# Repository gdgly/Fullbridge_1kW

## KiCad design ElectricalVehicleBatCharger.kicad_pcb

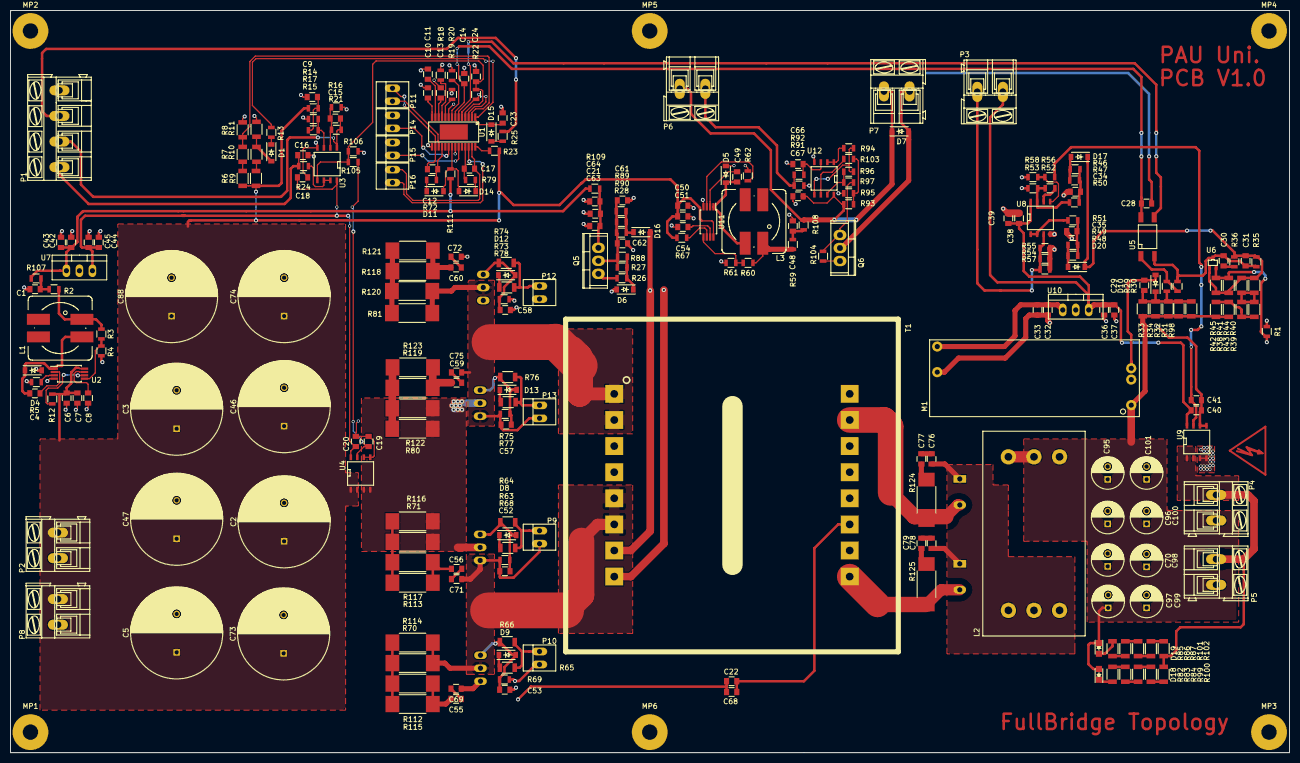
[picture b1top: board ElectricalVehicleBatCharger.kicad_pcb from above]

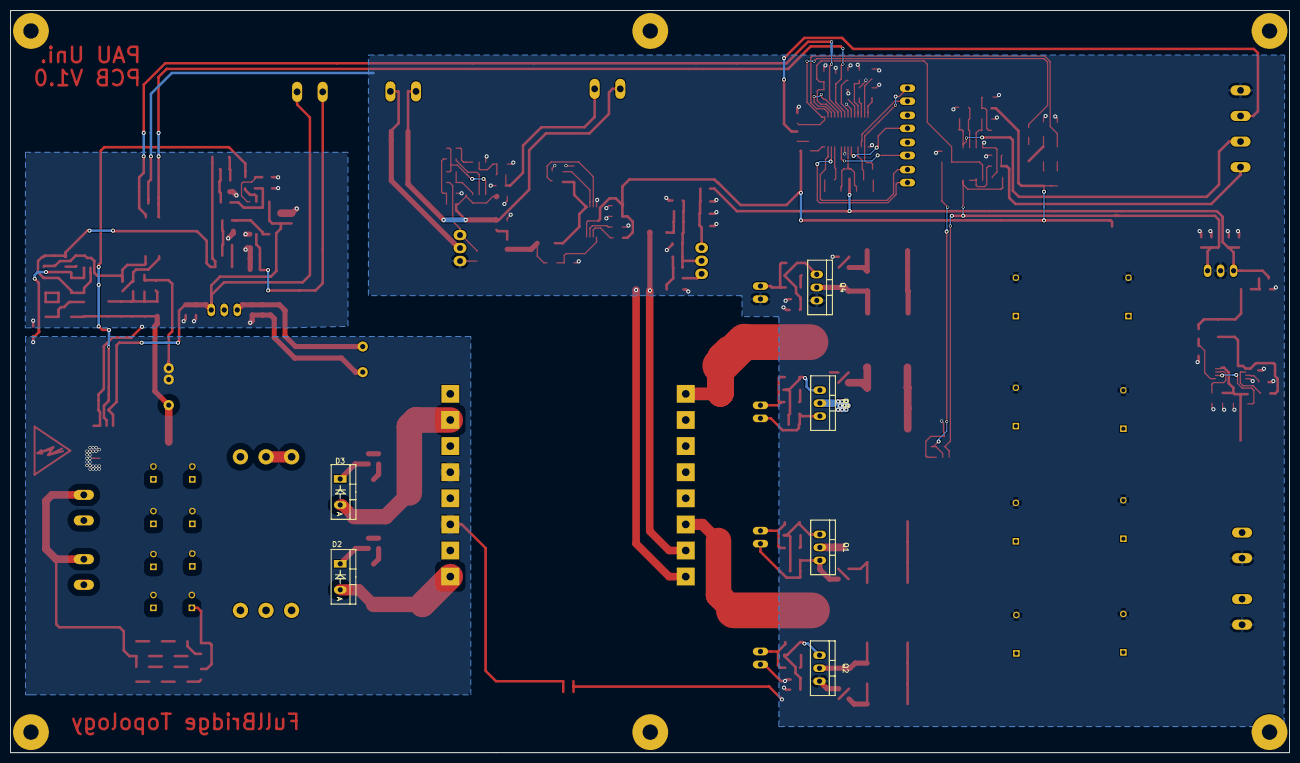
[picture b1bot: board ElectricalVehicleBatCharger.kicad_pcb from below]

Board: 2 copper layers, 249.9 x 145.0 mm, 271 parts (6 on the bottom side), 140 nets.

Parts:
C1, C4, C12, C17, C21, C48, C49, C62, C63, C64: CP1; C_0805
C2, C3, C5, C46, C47, C73, C74, C88: CP1; C_Radial_D18_L36_P7.5
C6, C7, C8, C9, C10, C11, C13, C14, C15, C23, C24, C28, C29, C30, C31, C32, C33, C34, C35, C36, C37, C38, C39, C42, C43, C44, C45, C50, C51, C52, C53, C54, C55, C56, C57, C58, C59, C60, C61, C66, C67, C69, C71, C72, C75, C76, C77, C78, C79: C; C_0805
C16, C18, C19: 1u; C_0805
C20, C22, C40, C41, C68: 100n; C_0805
C70, C95, C96, C97, C98, C99, C100, C101: CP1; C_Radial_D6.3_L11.2_P2.5
D1, D4, D5, D7, D8, D9, D11, D12, D13, D14, D15, D16, D17, D20: Diode; SOD-123
D2, D3: D_Schottky; Diode_TO-220_Vertical
D6, D10: ZENERsmall; SOD-123
D18: LED_Green; LED_0805
D19: LED_Red; LED_0805
L1, L3: INDUCTOR; Inductor_Double_SMD_12.5-Lx12.5-Wx6.2-H
L2: INDUCTOR_3; L_3
M1: Flyback; Flyback_Module_200mW
MP1, MP2, MP3, MP4, MP5, MP6: SCREW; SCREW_3mm
P1: CONN_01X04; AK300-4
P2, P3, P4, P5, P6, P7, P8: CONN_01X02; AK300-2
P9, P10, P11, P12, P13, P14, P15, P16: CONN_01X02; PINHEAD1-2
Q1, Q2, Q3, Q4: FDP083N15A; TO-220_Neutral123_Vertical
Q5: BD909; TO-220
Q6: IRF540N; TO-220
R1, R2, R3, R4, R5, R12, R13, R14, R15, R16, R17, R18, R19, R20, R21, R22, R23, R24, R25, R26, R27, R28, R29, R30, R35, R36, R46, R47, R48, R49, R50, R51, R52, R53, R54, R55, R56, R57, R58, R59, R60, R61, R62, R67, R68, R69, R72, R77, R78, R79, R88, R89, R90, R91, R92, R93, R94, R95, R96, R97, R104, R105, R106: R; R_0805
R6, R7, R8, R9, R10, R11, R31, R32, R33, R34, R38, R39, R40, R41, R42, R43, R44, R45, R63, R64, R65, R66, R73, R74, R75, R76, R98: R; R_1206
R70, R71, R80, R81, R112, R113, R114, R115, R116, R117, R118, R119, R120, R121, R122, R123, R124, R125: R; R_2512_HandSoldering
R82, R83, R84, R85, R86, R87, R99, R100, R101, R102: 22k; R_1206
R103: 10k; R_0805
R107, R108, R109: 0; R_0805
R111: NC; R_0805
T1: Transf_Type1; E65_Former
U1: LM5045; HTSSOP_9.70mmX4.40mm
U2, U11: LM5008; TSSOP-8_4.4x3mm_Pitch0.65mm
U3, U8, U12: LM358N; SOIC-8-N
U4, U9: ACS723; SOIC-8-N
U5: FOD817; Optocoupler_SMD_HandSoldering_KPC357_LTV35x_PC357_SingleCha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
U6: TL431; SOT-323
U7, U10: 7805; TO-220_Neutral123_Vertical

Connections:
+5V: C18.2, C20.2, C44.2, C45.2, U3.8, U4.8, U7.3
+5VD: C36.2, C37.2, C38.1, C39.2, C40.1, P3.1, U8.8, U9.8, U10.3
+12P: C32.2, C33.2, M1.5, U10.1
+12V: C67.1, D7.1, P6.2, P7.1, R93.1, R108.1, U12.8
+15V: C42.2, C43.2, R107.1, R109.2, R111.2, U7.1
/COMP: U1.6, U5.3
/Fan-: D7.2, P7.2, Q6.2
/HO1: P16.1, U1.26
/HO2: P11.1, U1.17
/Ip: C24.2, R22.1, R105.2, R106.1, U1.4, U3.5
/IpFiltered: C16.2, P1.1, R24.2
/LO1: P15.1, U1.23
/LO2: P14.1, U1.20
/Lo_Line: C76.2, C78.2, D2.1, D3.1, L2.1, L2.2, L2.3
/OVP: R7.2, R8.1, U1.2
/OnOff: P1.3, R25.1
/OutputPowerLine: C70.1, C95.1, C96.1, C97.1, C98.1, C99.1, C100.1, C101.1, D18.2, D19.1, L2.4, L2.5, L2.6, M1.1, P4.2, P5.2, R31.1, R32.1, R33.1, R34.1, R38.1, R42.1, R98.1
/OutputPowerLine_Return: P4.1, P5.1, R100.2, R102.2, U9.1, U9.2
/Q1_G: P9.2, R63.2, R64.2
/Q1_S: C52.1, C71.1, P9.1, Q1.3, Q2.2, R68.2, R70.1, R114.1, T1.5, T1.6
/Q2_G: P10.2, R65.2, R66.2
/Q3_G: P13.2, R75.2, R76.2
/Q3_S: C57.1, C75.2, P13.1, Q3.3, Q4.2, R77.2, R81.1, R120.1, T1.1, T1.2
/Q4_G: P12.2, R73.2, R74.2
/REF: C14.2, C28.1, U1.7, U5.4
/SHUTDOWN: R12.1, U2.6
/SHUTDOWN_FAN: R67.1, U11.6
/TR_9: D2.2, R125.2, T1.9
/TR_15: D3.2, R124.2, T1.15
/UVLO: C23.1, D15.1, R13.1, U1.1
/Vpwr: Q1.2, Q3.2, R71.1, R80.1, R116.1, R122.1, U4.3, U4.4
/Vsupercap: C15.2, P1.2, R21.2, U3.1
GND: C32.1, C33.1, C34.1, C35.1, C36.1, C37.1, C38.2, C39.1, C40.2, C41.2, M1.4, R1.1, R53.1, R54.2, R55.2, R57.2, R58.1, U8.4, U9.5, U9.6, U10.2
GNDD: C1.2, C2.2, C3.2, C5.2, C6.2, C7.2, C8.2, C9.1, C10.1, C11.1, C13.1, C14.1, C16.1, C18.1, C19.1, C20.1, C21.2, C22.1, C23.2, C24.1, C28.2, C42.1, C43.1, C44.1, C45.1, C46.2, C47.2, C48.2, C50.2, C51.2, C53.1, C54.2, C58.1, C61.1, C62.2, C63.2, C64.2, C66.1, C67.2, C68.1, C69.1, C72.1, C73.2, C74.2, C88.2, D4.2, D5.2, D6.2, P1.4, P2.1, P8.1, P10.1, P12.1, Q2.3, Q4.3, Q6.3, R4.1, R5.1, R8.2, R11.2, R16.1, R17.2, R18.1, R19.1, R20.1, R61.1, R62.1, R69.2, R78.2, R91.1, R95.2, R104.2, R106.2, T1.8, U1.9, U1.15, U1.22, U2.4, U3.4, U4.5, U4.6, U7.2, U11.4, U12.4
GNDREF: C22.2, C29.2, C68.2, C70.2, C95.2, C96.2, C97.2, C98.2, C99.2, C100.2, C101.2, D10.2, M1.2, M1.3, R1.2, R41.1, R45.2, T1.11, T1.13, U6.2, U9.3, U9.4
HS1: C17.2, P16.2, U1.27
HS2: C12.2, P11.2, U1.16
unnamed: C1.1, R2.1, R107.2
unnamed: C4.1, U2.2
unnamed: C4.2, D4.1, L1.2, U2.1
unnamed: C8.1, U2.7
unnamed: C9.2, R14.2, R15.1
unnamed: C10.2, U1.14
unnamed: C11.2, U1.13
unnamed: C12.1, R72.2, U1.18
unnamed: C13.2, U1.12
unnamed: C15.1, R16.2, R21.1, U3.2
unnamed: C17.1, R79.1, U1.25
unnamed: C19.2, R105.1, U4.7
unnamed: C21.1, C63.1, C64.1, Q5.3, R109.1
unnamed: C29.1, D10.1, R29.2, R31.2, R32.2, R33.2, R34.2, R98.2
unnamed: C30.1, C31.1, R30.2, R35.1, U5.2, U6.3
unnamed: C30.2, R36.1
unnamed: C31.2, D17.1, D20.1, R35.2, R36.2, R40.1, R41.2, R44.2, R45.1, U6.1
unnamed: C34.2, R46.1, R47.1, R50.2
unnamed: C35.2, R48.1, R49.1, R51.2
unnamed: C41.1, R56.1, U9.7
unnamed: C48.1, R59.1, R108.2
unnamed: C49.1, U11.2
unnamed: C49.2, D5.1, L3.2, U11.1
unnamed: C52.2, D8.2, Q1.1, R64.1, R68.1
unnamed: C53.2, D9.2, Q2.1, R66.1, R69.1
unnamed: C54.1, U11.7
unnamed: C55.1, C69.2
unnamed: C55.2, R112.2, R115.2
unnamed: C56.1, C71.2
unnamed: C56.2, R113.2, R117.2
unnamed: C57.2, D13.2, Q3.1, R76.1, R77.1
unnamed: C58.2, D12.2, Q4.1, R74.1, R78.1
unnamed: C59.1, C75.1
unnamed: C59.2, R119.2, R123.2
unnamed: C60.1, C72.2
unnamed: C60.2, R118.2, R121.2
unnamed: C61.2, C62.1, Q5.2, R27.2, R28.2, R88.2, R89.2, R90.2
unnamed: C66.2, R92.2, U12.3
unnamed: C76.1, C77.2
unnamed: C77.1, R124.1
unnamed: C78.1, C79.2
unnamed: C79.1, R125.1
unnamed: D1.1, R13.2
unnamed: D1.2, R10.2, R11.1
unnamed: D6.1, R26.1, R27.1, R88.1
unnamed: D8.1, R63.1
unnamed: D9.1, R65.1
unnamed: D11.1, R72.1
unnamed: D12.1, R73.1
unnamed: D13.1, R75.1
unnamed: D14.1, R79.2
unnamed: D15.2, R25.2
unnamed: D16.1, R28.1, R89.1, R90.1
unnamed: D16.2, T1.7
unnamed: D17.2, R46.2, R47.2
unnamed: D18.1, R82.1
unnamed: D19.2, R85.1
unnamed: D20.2, R48.2, R49.2
unnamed: L1.1, R2.2, R3.2
unnamed: L3.1, R59.2, R60.2
unnamed: P3.2, R54.1, R55.1, R57.1, U8.3
unnamed: P6.1, R91.2, R92.1
unnamed: Q5.1, R26.2
unnamed: Q6.1, R97.2, R104.1
unnamed: R3.1, R4.2, U2.5
unnamed: R5.2, U2.3
unnamed: R6.2, R7.1
unnamed: R9.2, R10.1
unnamed: R15.2, R17.1, U3.3
unnamed: R18.2, U1.11
unnamed: R19.2, U1.10
unnamed: R20.2, U1.8
unnamed: R22.2, U1.3, U1.5
unnamed: R23.2, U1.28
unnamed: R24.1, U3.6, U3.7
unnamed: R29.1, R30.1, U5.1
unnamed: R38.2, R39.1, R42.2, R43.1
unnamed: R39.2, R40.2, R43.2, R44.1
unnamed: R50.1, R52.1, R53.2, U8.7
unnamed: R51.1, U8.1, U8.2
unnamed: R52.2, U8.6
unnamed: R56.2, R58.2, U8.5
unnamed: R60.1, R61.2, U11.5
unnamed: R62.2, U11.3
unnamed: R82.2, R83.1
unnamed: R83.2, R84.1
unnamed: R84.2, R99.1
unnamed: R85.2, R86.1
unnamed: R86.2, R87.1
unnamed: R94.1, R96.1, U12.5
unnamed: R94.2, U12.1, U12.2
unnamed: R96.2, R97.1, U12.7
unnamed: R99.2, R100.1
unnamed: R87.2, R101.1
unnamed: R101.2, R102.1
unnamed: R103.1, U12.6
unnamed: R93.2, R95.1, R103.2
unnamed: R70.2, R112.1, R114.2, R115.1
unnamed: R71.2, R113.1, R116.2, R117.1
unnamed: R81.2, R118.1, R120.2, R121.1
unnamed: R80.2, R119.1, R122.2, R123.1
VAA: C2.1, C3.1, C5.1, C6.1, C7.1, C46.1, C47.1, C50.1, C51.1, C73.1, C74.1, C88.1, P2.2, P8.2, R6.1, R9.1, R12.2, R14.1, R23.1, R67.2, U2.8, U4.1, U4.2, U11.8
VCC: D11.2, D14.2, R111.1, U1.21

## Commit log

2016-10-29 25W ve 60W test edilmis devre.
